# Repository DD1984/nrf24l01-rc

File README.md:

# nRF24-based RC car receiver, compatible with HobbyKing HK310 and Turnigy 3XS

This project includes **electronics** and **firmware** to build **surface RC receivers** that can replace the HobbyKing [HKR3000](http://hobbyking.com/hobbyking/store/__12187__HK_3000_3ch_2_4ghz_FHSS_RX_suit_the_HK310_Transmitter.html) and [XR3100](http://hobbyking.com/hobbyking/store/__22910__HK3100_3ch_2_4ghz_FHSS_Micro_RX_suits_HK310_Turnigy_3XS_TX_.html) receivers. They can be used with the [HK300](http://hobbyking.com/hobbyking/store/__12177__HK_300_3_Channel_2_4ghz_FHSS_Ground_Radio.html), [HK310](http://hobbyking.com/hobbyking/store/__12181__HK_310_3_Channel_2_4ghz_FHSS_Ground_Radio.html) and [Turnigy 3XS](http://hobbyking.com/hobbyking/store/__24905__Turnigy_3XS_FHSS_2_4GHz_3_Channel_Radio_System.html) RC car radio systems.

The receivers make use of off-the-shelf inexpensive RF modules.

Two variants are provided:

- [lpc812-nrf24l01](lpc812-nrf24l01-receiver/): NRF24L01+ module plus a [NXP LPC812](http://www.nxp.com/products/microcontrollers/cortex_m0_m0/series/LPC800.html) MCU
- [nrf24le1](nrf24le1-receiver/): Using a NRF24LE1 module (integrated 8051 MCU)

**Now the third variant is available:**

- [stm32-nrf24l01](stm32-nrf24l01-receiver/): NRF24L01+ module plus a cheap STM32F030F4P6 MCU

**Fourth variant is available:**
- [stm32-nrf24l01](stm32-nrf24l01-receiver/): NRF24L01+ module (smd mount) plus a STM32F100C4T6 MCU (work on stm32vldiscovery too)

Technical information about the inner working of the receivers can be found
in **[hkr3000-info.md](doc/hkr3000-info.md)**.

## Advantages of the NRF24L01+ - LPC812 version

- Easily obtainable and very low cost NRF module (less than USD 1 including shipping in qty 10 on eBay, Aliexpress)
- Very precise servo pulses due to LPC812 timer hardware
- ARM Cortex-M0 32-bit CPU is easy to program for with the GCC ARM compiler
- No proprietary programmer required as the MCU has a ROM bootloader that can be flashed with an  USB-to-serial dongle
- Servo pulses can be updated down to every 5 ms (200 Hz). In theory this may provide better response but in practice the transmitter would need to be modified to fully take
advantage of this fact.
- UART output using the LANE Boys RC [preprocessor protocol](http://laneboysrc.blogspot.com/2012/12/pre-processor-for-diy-rc-light.html), e.g. to hook up the [DIY RC light controller](https://github.com/laneboysrc/rc-light-controller) with a single servo cable.

Downsides:

- Requires a PCB and intermediate SMD soldering skills
- No CPPM output (but it has a UART output that can carry CPPM-like data and more)

## Advantages of the NRF24LE1 version

- Low part count: NRF24LE1 module, voltage regulator, a few capacitors; done!
- Simple to build even on a breadboard
- CPPM output
- UART output using the LANE Boys RC [preprocessor protocol](http://laneboysrc.blogspot.com/2012/12/pre-processor-for-diy-rc-light.html), e.g. to hook up the [DIY RC light controller](https://github.com/laneboysrc/rc-light-controller) with a single servo cable. Baudrate is limited to 38400 though.

Downsides:

- NRF24LE1 module is more expensive than NRF24L01 and harder to find
- Requires special programming hardware. Multiple open-source versions can be found on the Internet.
- Servo pulses are software timed, hence slightly jittery despite using interrupts. Note that the firmware included in this project is improved over the original HKR3000 and XR3100 firmware, which regularly extends servo pulses by 16 us due to poor interrupt logic implementation.
- For the PCB provided in this project you need to get the NRF24LE1 module version that has an SMD crystal (size 21 x 15 mm)

The NRF24LE1 firmware included in this project can be compiled to be compatible with the HKR3000 and XR3100 hardware. However, since those receivers use the OTP version (NRF24LE1G) one would have to replace the chip with the NR24LE1E versions to be able to use it.

## Advantages of the NRF24L01+ - STM32F0 version

- Cheap and easily accessible MCU
- Free version of Keil MDK for STM32F0
- precise PWM due to hardware timer
- PWM frequency up to 200 Hz independ for CH1 and CH2/CH3
- One sided PCB with two jumper wire only

Downsides:

- 3 channel PWM output only

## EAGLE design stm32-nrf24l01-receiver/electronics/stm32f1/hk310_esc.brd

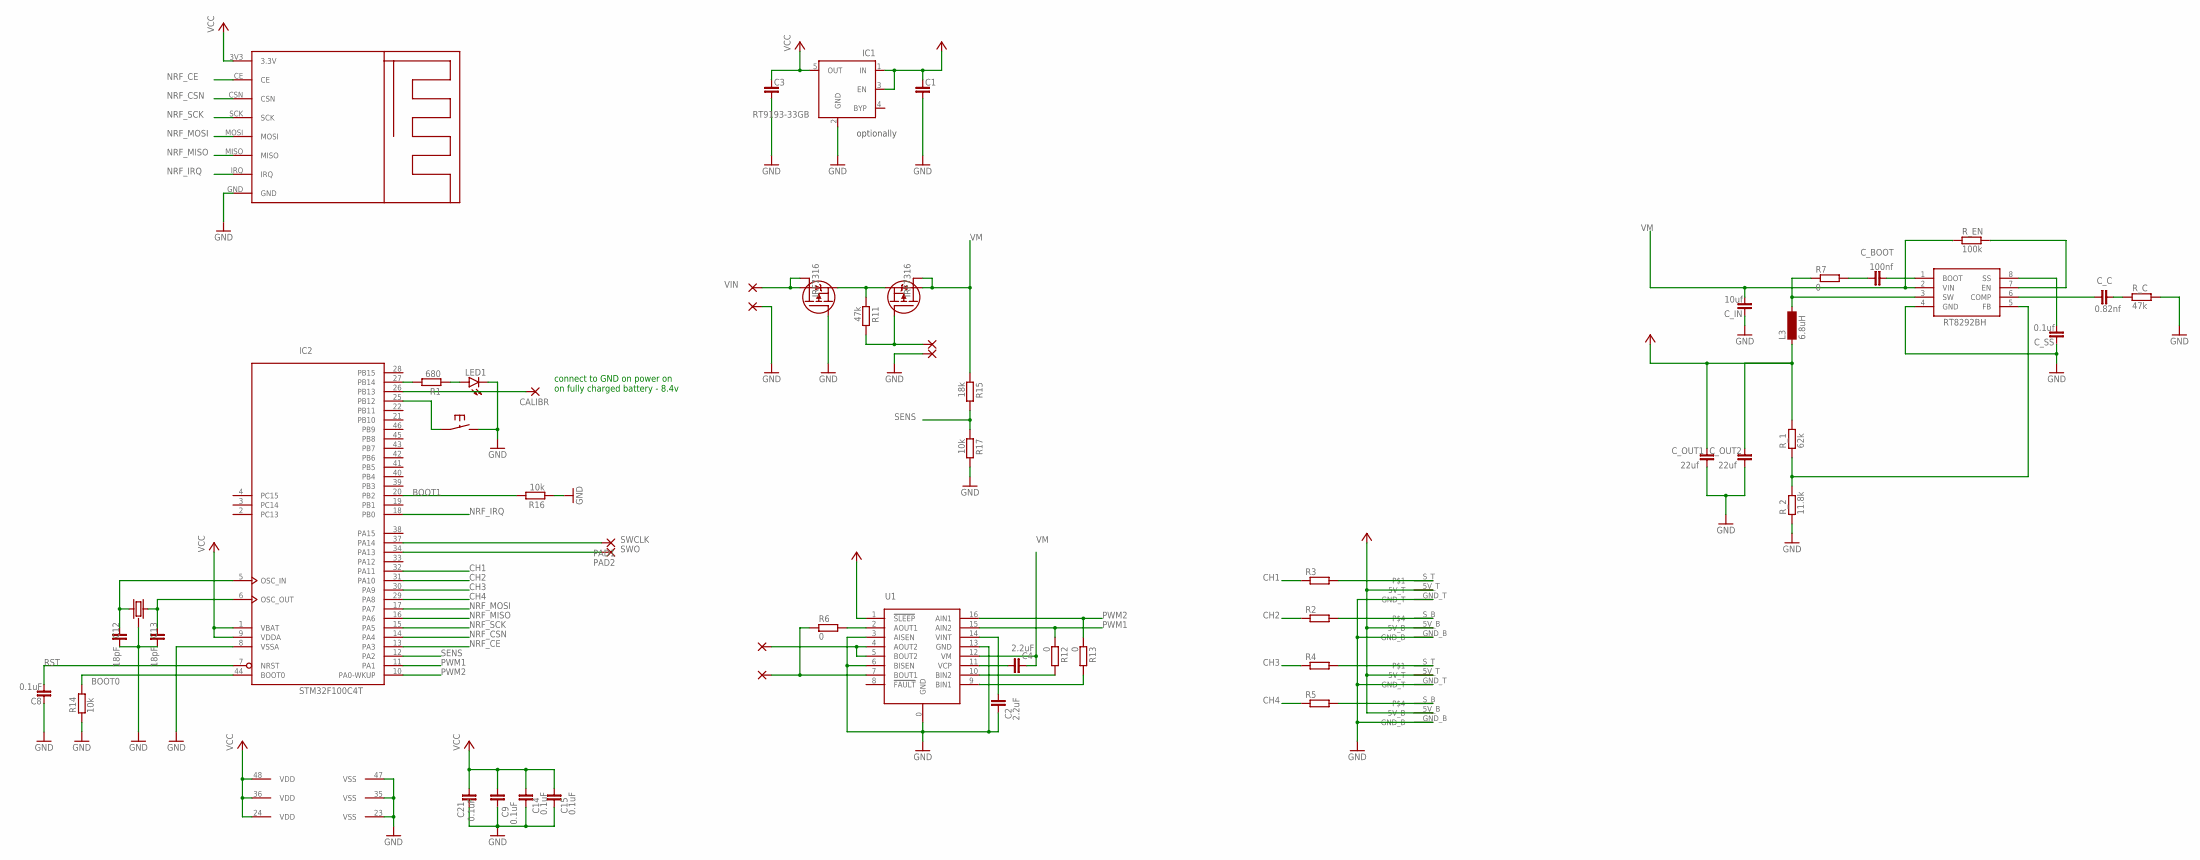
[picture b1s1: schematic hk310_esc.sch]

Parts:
C1, C3: C_0805; C0805
C2, C4: 2.2uF; C0805
C8, C9, C14, C15, C21: 0.1uF; C0603
C12, C13: 18pF; C0603
CALIBR: SMD2; SMD1,27-2,54
C_BOOT: 100nf; C0402
C_C: 0.82nf; C0402
C_IN: 10uf; C1206
C_OUT1, C_OUT2: 22uf; C0805
C_SS: 0.1uf; C0402
IC1: RT9193-33GB; SOT23-5
IC2: STM32F100C4T; LQFP48
L3: 6.8uH; MS85
LED1: LED; SMARTLED-TTW
PAD1, PAD2: SMD2; SMD1,27-2,54
PAD3, PAD4, PAD5, PAD6, PAD7, PAD8: WIREPADSMD5-1,8; 5-1,8
R1: 680; R0805
R2, R3, R4, R5: R-EU_R1206; R1206
R6, R7, R12, R13: 0; R1206
R11: 47k; R0805
R14, R16, R17: 10k; R0805
R15: 18k; R0805
RT8292BH: RT8292B; SO8-2
R_1: 62k; R0402
R_2: 11.8k; R0402
R_C: 47k; R0402
R_EN: 100k; R0402
U1: DRV8833; PWP16
U$1: NRF24MINI
U$2, U$3: PINHEAD_SMD
U$5: IRF7104; SO8-2
U$6: 8Mhz; CRYSTAL_3PINS
U$7: SMALL_BUTTON

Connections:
+5V: C1.1, C_OUT1.2, C_OUT2.2, IC1.1 (IN), IC1.3 (EN), L3.1, R_1.2, U1.1 (!SLEEP), U$2.5V_B, U$2.5V_T, U$3.5V_B, U$3.5V_T
BOOT0: IC2.44 (BOOT0), R14.2
BOOT1: IC2.20 (PB2), R16.2
CH1: IC2.32 (PA11), R3.1
CH2: IC2.31 (PA10), R2.1
CH3: IC2.30 (PA9), R4.1
CH4: IC2.29 (PA8), R5.1
GND: C1.2, C2.1, C3.2, C8.1, C9.1, C12.1, C13.1, C14.1, C15.1, C21.1, C_IN.1, C_OUT1.1, C_OUT2.1, C_SS.1, IC1.2 (GND), IC2.8 (VSSA), IC2.23 (VSS), IC2.35 (VSS), IC2.47 (VSS), LED1.C@1 (C), PAD5.1, PAD8.1, R14.1, R16.1, R17.2, RT8292BH.4 (GND), R_2.1, R_C.2, U1.0 (GND), U1.3 (AISEN), U1.6 (BISEN), U1.13 (GND), U$1.GND, U$2.GND_B, U$2.GND_T, U$3.GND_B, U$3.GND_T, U$5.4 (G), U$6.GND, U$7.2_1 (2), U$7.2_2 (2)
unnamed: IC2.25 (PB12), U$7.1_1 (1), U$7.1_2 (1)
unnamed: IC2.27 (PB14), R1.2
unnamed: LED1.A@1 (A), R1.1
unnamed: PAD3.1, U1.4 (AOUT2), U1.5 (BOUT2)
unnamed: R6.2, U1.2 (AOUT1)
unnamed: C2.2, U1.14 (VINT)
unnamed: C4.2, U1.11 (VCP)
unnamed: CALIBR.1, IC2.26 (PB13)
unnamed: C12.2, IC2.5 (OSC_IN), U$6.P$1
unnamed: R12.2, U1.10 (BIN2)
unnamed: R3.2, U$2.S_T
unnamed: R2.2, U$2.S_B
unnamed: R4.2, U$3.S_T
unnamed: R5.2, U$3.S_B
unnamed: PAD7.1, R6.1, U1.7 (BOUT1)
unnamed: C_BOOT.1, R7.2
unnamed: C13.2, IC2.6 (OSC_OUT), U$6.P$2
unnamed: PAD6.1, R11.2, U$5.2 (G)
unnamed: R13.2, U1.9 (BIN1)
unnamed: RT8292BH.7 (EN), R_EN.2
unnamed: C_SS.2, RT8292BH.8 (SS)
unnamed: C_BOOT.2, RT8292BH.1 (BOOT)
unnamed: L3.2, R7.1, RT8292BH.3 (SW)
unnamed: RT8292BH.5 (FB), R_1.1, R_2.2
unnamed: C_C.2, R_C.1
unnamed: C_C.1, RT8292BH.6 (COMP)
NRF_CE: IC2.13 (PA3), U$1.CE
NRF_CSN: IC2.14 (PA4), U$1.CSN
NRF_IRQ: IC2.18 (PB0), U$1.IRQ
NRF_MISO: IC2.16 (PA6), U$1.MISO
NRF_MOSI: IC2.17 (PA7), U$1.MOSI
NRF_SCK: IC2.15 (PA5), U$1.SCK
PWM1: IC2.11 (PA1), R12.1, U1.15 (AIN2)
PWM2: IC2.10 (PA0-WKUP), R13.1, U1.16 (AIN1)
RST: C8.2, IC2.7 (NRST)
SENS: IC2.12 (PA2), R15.2, R17.1
SWCLK: IC2.37 (PA14), PAD1.1
SWO: IC2.34 (PA13), PAD2.1
VCC: C3.1, C9.2, C14.2, C15.2, C21.2, IC1.5 (OUT), IC2.1 (VBAT), IC2.9 (VDDA), IC2.24 (VDD), IC2.36 (VDD), IC2.48 (VDD), U$1.3V3 (3.3V)
VIN: PAD4.1, U$5.5 (D), U$5.6 (D)
VIN_PROT: R11.1, U$5.1 (S), U$5.3 (S)
VM: C4.1, C_IN.2, R15.1, RT8292BH.2 (VIN), R_EN.1, U1.12 (VM), U$5.7 (D), U$5.8 (D)

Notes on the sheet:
optionally
connect to GND on power on on fully charged battery - 8.4v

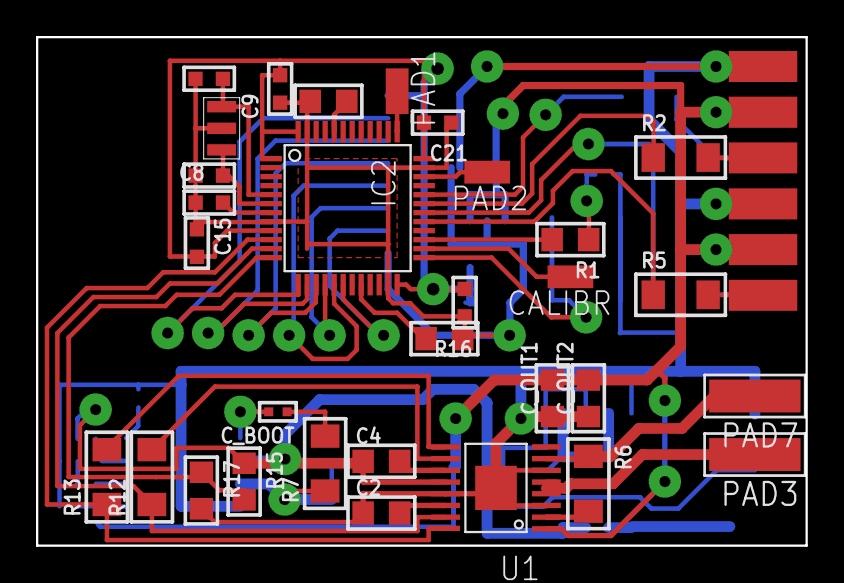
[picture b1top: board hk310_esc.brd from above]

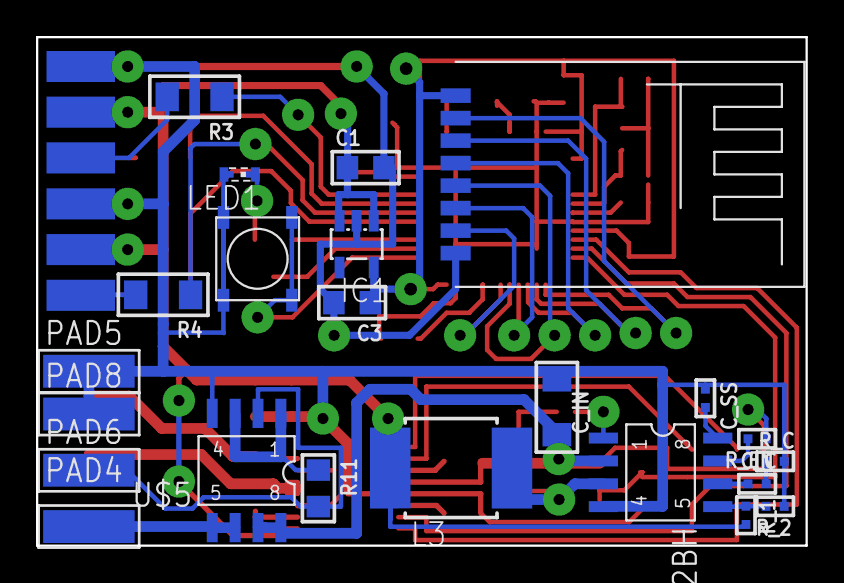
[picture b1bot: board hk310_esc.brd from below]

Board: 2 copper layers, 42.8 x 28.2 mm, 56 parts (25 on the bottom side), 50 nets.

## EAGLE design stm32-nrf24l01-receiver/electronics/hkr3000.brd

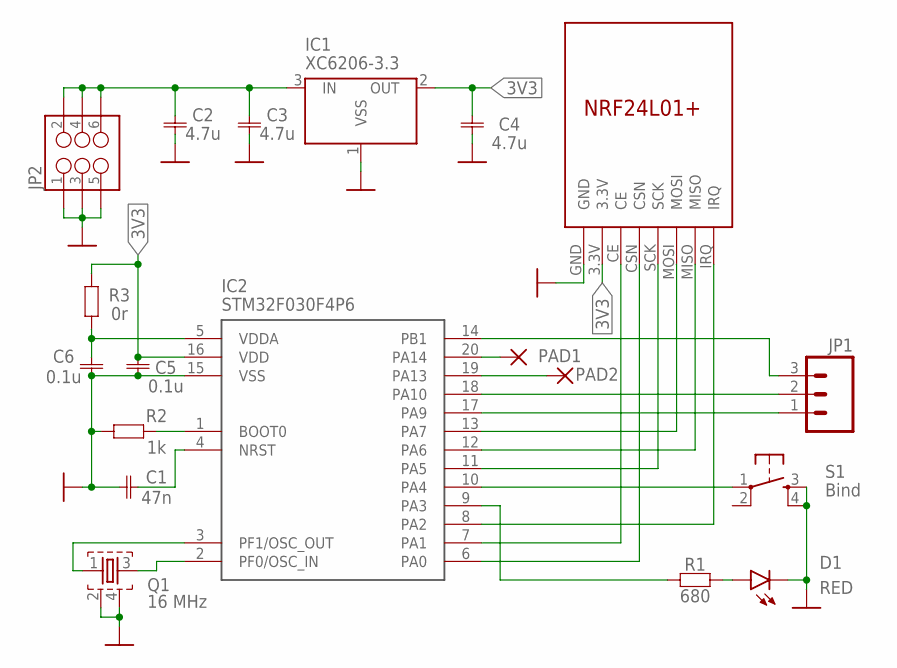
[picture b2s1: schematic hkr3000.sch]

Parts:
C1: 47n; 0402
C2, C3, C4: 4.7u; 0805
C5, C6: 0.1u; 0402
D1: RED; LED-0603
IC1: XC6206-3.3; XC6206_SOT-23
IC2: STM32F030F4P6; TSSOP-20
JP1: M03PTH; 1X03
JP2: M03X2POGO_PINS; 2X3_POGO
PAD1, PAD2: SMD2; SMD1,27-2,54
Q1: 16 MHz; FA-20H
R1: 680; 0402
R2: 1k; 0402
R3: 0r; 0603
S1: Bind; TACTILE-PTH
U$1: NRF24L01

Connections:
3V3: C4.P$2, C5.P$2, IC1.2 (OUT), IC2.16 (VDD), R3.P$2, U$1.3.3V
3V3-1: C6.P$2, IC2.5 (VDDA), R3.P$1
GND: C1.P$1, C2.P$1, C3.P$1, C4.P$1, C5.P$1, C6.P$1, D1.C, IC1.1 (VSS), IC2.15 (VSS), JP2.P$1 (1), JP2.P$3 (3), JP2.P$5 (5), Q1.2, Q1.4, R2.P$1, S1.3, S1.4, U$1.GND
unnamed: C2.P$2, C3.P$2, IC1.3 (IN), JP2.P$2 (2), JP2.P$4 (4), JP2.P$6 (6)
unnamed: D1.A, R1.P$2
unnamed: IC2.20 (PA14), PAD1.1
unnamed: IC2.11 (PA5), U$1.SCK
unnamed: IC2.12 (PA6), U$1.MISO
unnamed: IC2.13 (PA7), U$1.MOSI
unnamed: IC2.17 (PA9), JP1.1
unnamed: IC2.18 (PA10), JP1.2
unnamed: IC2.14 (PB1), JP1.3
unnamed: IC2.2 (PF0/OSC_IN), Q1.3
unnamed: IC2.3 (PF1/OSC_OUT), Q1.1
unnamed: C1.P$2, IC2.4 (NRST)
unnamed: IC2.1 (BOOT0), R2.P$2
unnamed: IC2.9 (PA3), R1.P$1
unnamed: IC2.19 (PA13), PAD2.1
unnamed: IC2.7 (PA1), U$1.CE
unnamed: IC2.6 (PA0), U$1.CSN
unnamed: IC2.8 (PA2), U$1.IRQ
unnamed: IC2.10 (PA4), S1.1

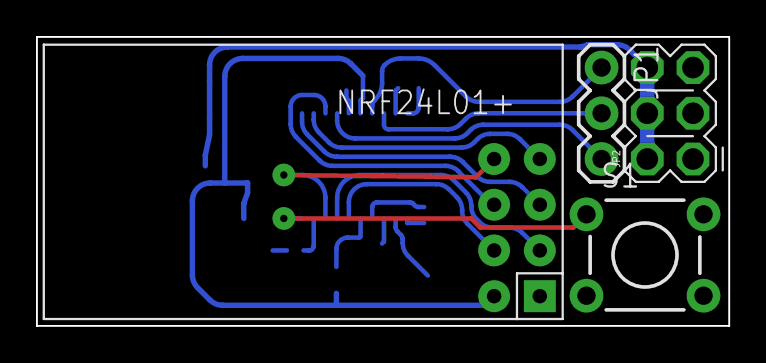
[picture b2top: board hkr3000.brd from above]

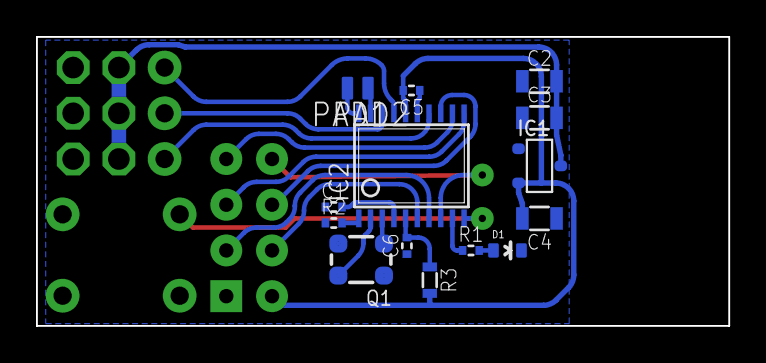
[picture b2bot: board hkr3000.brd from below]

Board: 2 copper layers, 38.5 x 16.1 mm, 19 parts (15 on the bottom side), 22 nets.

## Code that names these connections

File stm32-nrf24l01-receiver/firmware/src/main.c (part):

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{
#ifdef STM32F1
    /**
     * PB14    - LED
     * PB13    - BAT CALIBR
     * PB12    - BIND
     *
     * PA4     - NRF_CSN
     * PA3     - NRF_CE
     * PB0     - NRF_IRQ
     * PA5     - NRF_SCK
     * PA6     - NRF_MISO
     * PA7     - NRF_MOSI
     *
     * PA11    - CH1 - TIM1_CH4
     * PA10    - CH2 - TIM1_CH3
     * PA9     - CH3 - TIM1_CH2
     * PA8     - CH4 - TIM1_CH1 - for future use
     */
    /* GPIO config */
    RCC->APB2ENR |= RCC_APB2ENR_IOPAEN | RCC_APB2ENR_IOPBEN | RCC_APB2ENR_IOPCEN | RCC_APB2ENR_AFIOEN;
    //PB14 - LED
    GPIOB->CRH &= ~(GPIO_CRH_CNF14 | GPIO_CRH_MODE14);
    GPIOB->CRH |= GPIO_CRH_MODE14_1; //2mhz out push-pull
    //PB12 - BIND
    GPIOB->CRH &= ~(GPIO_CRH_CNF12 | GPIO_CRH_MODE12);
    GPIOB->CRH |= GPIO_CRH_CNF12_1; //input push-pull
    GPIOB->BSRR = GPIO_BSRR_BS12; //pull up
#ifdef ESC
    //PB13 - BAT CALIBR
    GPIOB->CRH &= ~(GPIO_CRH_CNF13 | GPIO_CRH_MODE13);
    GPIOB->CRH |= GPIO_CRH_CNF13_1; //input push-pull
    GPIOB->BSRR = GPIO_BSRR_BS13; //pull up
#endif

    //PA4 - NRF_CSN, PA3 - NRF_CE
    GPIOA->CRL &= ~(GPIO_CRL_CNF4 | GPIO_CRL_MODE4 | GPIO_CRL_CNF3 | GPIO_CRL_MODE3);
    GPIOA->CRL |= GPIO_CRL_MODE4_0 | GPIO_CRL_MODE3_0; //10mhz out push-pull
    //PB0 - NRF_IRQ
    GPIOB->CRL &= ~(GPIO_CRL_CNF0 | GPIO_CRL_MODE0);
    GPIOB->CRL |= GPIO_CRL_CNF0_1; //input push-pull
    GPIOB->BSRR = GPIO_BSRR_BS0; //pull up

    //PA5, PA7
    GPIOA->CRL &= ~(GPIO_CRL_CNF5 | GPIO_CRL_MODE5 | GPIO_CRL_CNF7 | GPIO_CRL_MODE7);
    GPIOA->CRL |= GPIO_CRL_CNF5_1 | GPIO_CRL_MODE5_0 | GPIO_CRL_CNF7_1 | GPIO_CRL_MODE7_0; //10mhz alt push-pull
    //PA6 - floating input (do nothing)

    //PA11, PA10, PA9, PA8
    GPIOA->CRH &= ~(GPIO_CRH_CNF11 | GPIO_CRH_MODE11
                 | GPIO_CRH_CNF10 | GPIO_CRH_MODE10
                 | GPIO_CRH_CNF9 | GPIO_CRH_MODE9
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#else

    /**
     * PA0     - NRF_CSN
     * PA1     - NRF_CE
     * PA2     - NRF_IRQ
     * PA3     - LED
     * PA4     - BIND
     * PA5     - NRF_SCK
     * PA6     - NRF_MISO
     * PA7     - NRF_MOSI
     * PA9     - CH3 - TIM1_CH2
     * PA10    - CH2 - TIM1_CH3
     * PB1     - CH1 - TIM14_CH1
     */
    /* GPIO config */
    RCC->AHBENR |= RCC_AHBENR_GPIOAEN | RCC_AHBENR_GPIOBEN;
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
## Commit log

2017-09-17 add stm32 port
2017-09-19 add watchdog
2017-09-19 add shematic and update README
2017-09-23 fix underflow
2020-05-23 [5/5] add servo output CH2, CH3 on TIM1
2020-05-23 [1/5] remove include stm32f0xx.h, because it included in platform.h
2020-05-23 [2/5] move startup files for stm32f0 in separated dir
2020-05-23 [3/5] add startup files for stm32f1 and Makefile
2020-05-23 [4/5] first work build for stm32vldiscovery, without channels output
2020-05-23 add stm32f1 linker script
2020-05-28 move stm32f0 PCB in separated dir
2020-05-28 add stm32f1 PCB
2020-05-28 - CH1 on TIM1 - change GPIOs for PCB - change ld script for stm32f100c4
2020-05-28 add firmware for stm32f1
2020-05-28 add stm32f1 version to readme
2020-05-28 readme: add info about stm32vldiscovery
2020-05-28 stm32f1 pcb photos
2020-06-01 stm32f1: add box 3d printing model
2020-07-13 add: - ESC support - battery health check (with calibration) - statup sound, batery level sound
    change:
    - persistent_storage - forsave many params
    - add uart debug
2020-07-13 pcb with esc
2020-07-13 esc fw
2020-07-14 esc stop fix
2020-07-15 fix battery health check

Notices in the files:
parts and their libraries:
SparkFun-Connectors: Licensing: Creative Commons ShareAlike 4.0 International - https://creativecommons.org/licenses/by-sa/4.0
irf-2: Copyright & License
This library is licensed under the General Public License, Version 2.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
